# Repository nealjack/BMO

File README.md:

BMO
===

Code, Art and Design files to make BMO from adventure time

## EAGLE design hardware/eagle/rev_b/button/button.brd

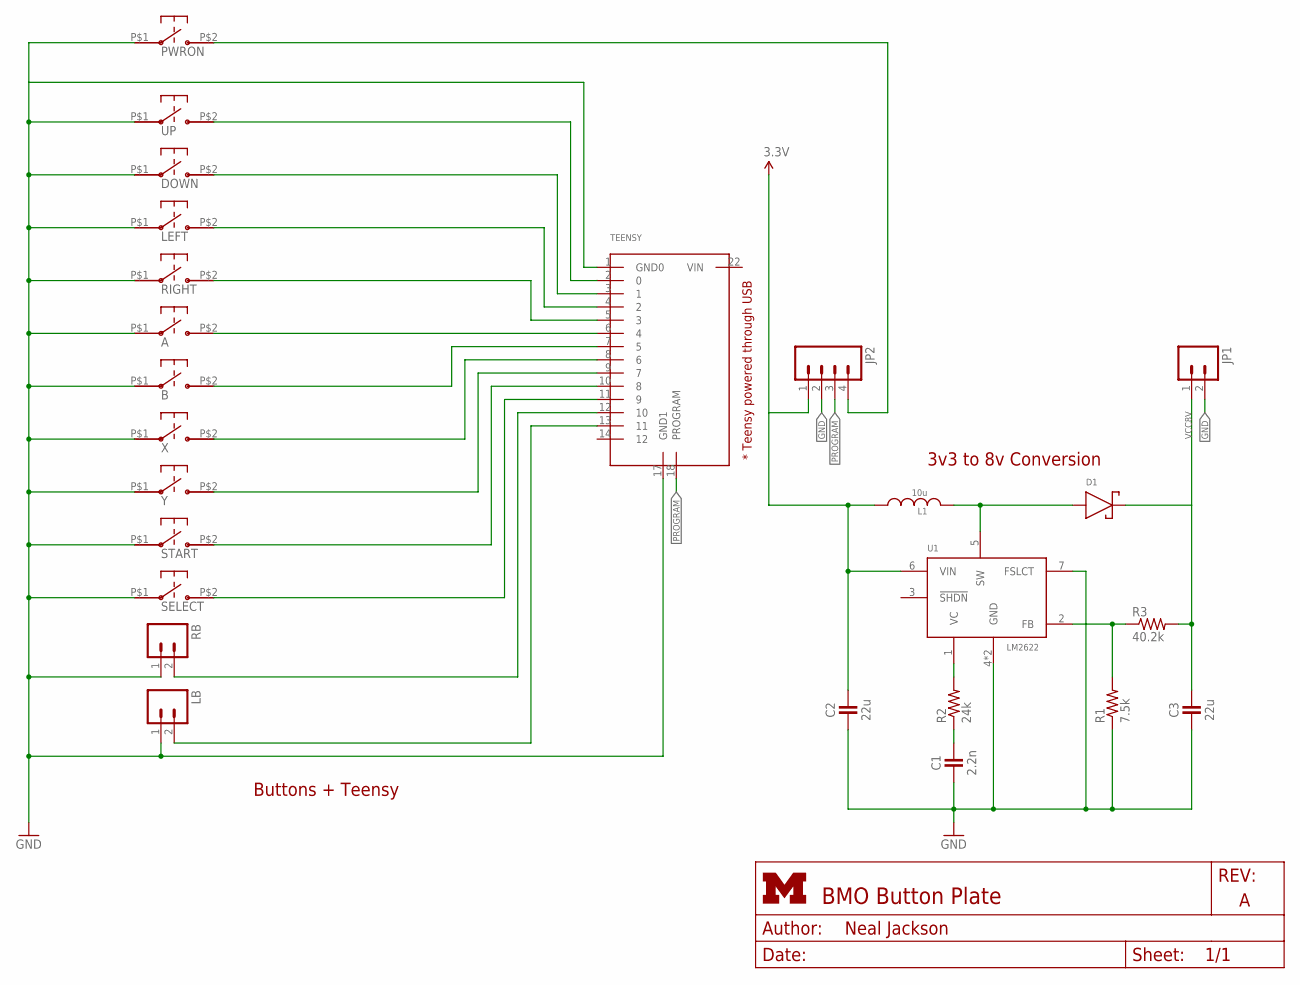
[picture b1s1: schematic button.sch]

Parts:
A: SKPDAMD010
B: SKPDAMD010
C1: 2.2n; 0402_CAP
C2, C3: 22u; 0402_CAP
D1: MBRM140T3G; DO-216AA
DOWN: SKPDAMD010
JP1: M02PTH; 1X02
JP2: M04PTH; 1X04
L1: 10u; 0402_CAP
LB: M02PTH; 1X02
LEFT: SKPDAMD010
PWRON: SKPDAMD010
R1: 7.5k; 0402_RES
R2: 24k; 0402_RES
R3: 40.2k; 0402_RES
RB: M02PTH; 1X02
RIGHT: SKPDAMD010
SELECT: EVQ11D09K
START: EVQ11D09K
TEENSY: TEENSY_LC
U1: LM2622; MSOP8
UP: SKPDAMD010
X: SKPDAMD010
Y: SKPDAMD010

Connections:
3.3V: C2.1, JP2.1, L1.1, U1.6 (VIN)
GND: A.P$1, B.P$1, C1.2, C2.2, C3.2, DOWN.P$1, JP1.2, JP2.2, LB.1, LEFT.P$1, PWRON.P$1, R1.1, RB.1, RIGHT.P$1, SELECT.P$1, START.P$1, TEENSY.1 (GND0), TEENSY.17 (GND1), U1.4 (GND), U1.7 (FSLCT), U1.GND, UP.P$1, X.P$1, Y.P$1
unnamed: A.P$2, TEENSY.6 (4)
unnamed: JP2.4, PWRON.P$2
unnamed: TEENSY.2 (0), UP.P$2
unnamed: DOWN.P$2, TEENSY.3 (1)
unnamed: LEFT.P$2, TEENSY.4 (2)
unnamed: RIGHT.P$2, TEENSY.5 (3)
unnamed: C1.1, R2.1
unnamed: B.P$2, TEENSY.7 (5)
unnamed: TEENSY.8 (6), X.P$2
unnamed: TEENSY.9 (7), Y.P$2
unnamed: START.P$2, TEENSY.10 (8)
unnamed: SELECT.P$2, TEENSY.11 (9)
unnamed: RB.2, TEENSY.12 (10)
unnamed: LB.2, TEENSY.13 (11)
unnamed: R2.2, U1.1 (VC)
unnamed: D1.ANODE, L1.2, U1.5 (SW)
unnamed: R1.2, R3.1, U1.2 (FB)
PROGRAM: JP2.3, TEENSY.18 (PROGRAM)
VCC8V: C3.1, D1.CATHODE, JP1.1, R3.2

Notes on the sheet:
* Teensy powered through USB
Buttons + Teensy
3v3 to 8v Conversion

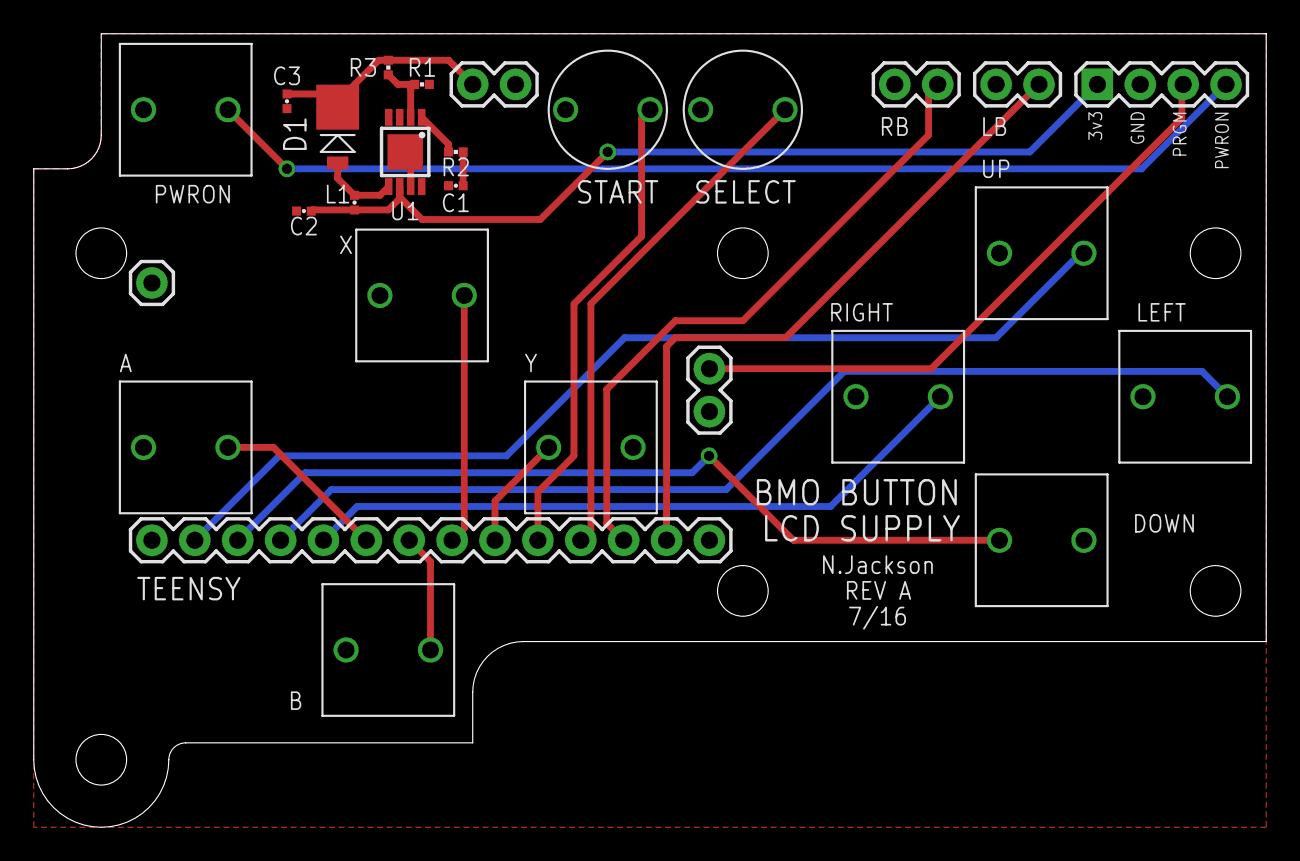
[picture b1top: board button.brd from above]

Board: 2 copper layers, 73.0 x 47.0 mm, 25 parts (0 on the bottom side), 21 nets.

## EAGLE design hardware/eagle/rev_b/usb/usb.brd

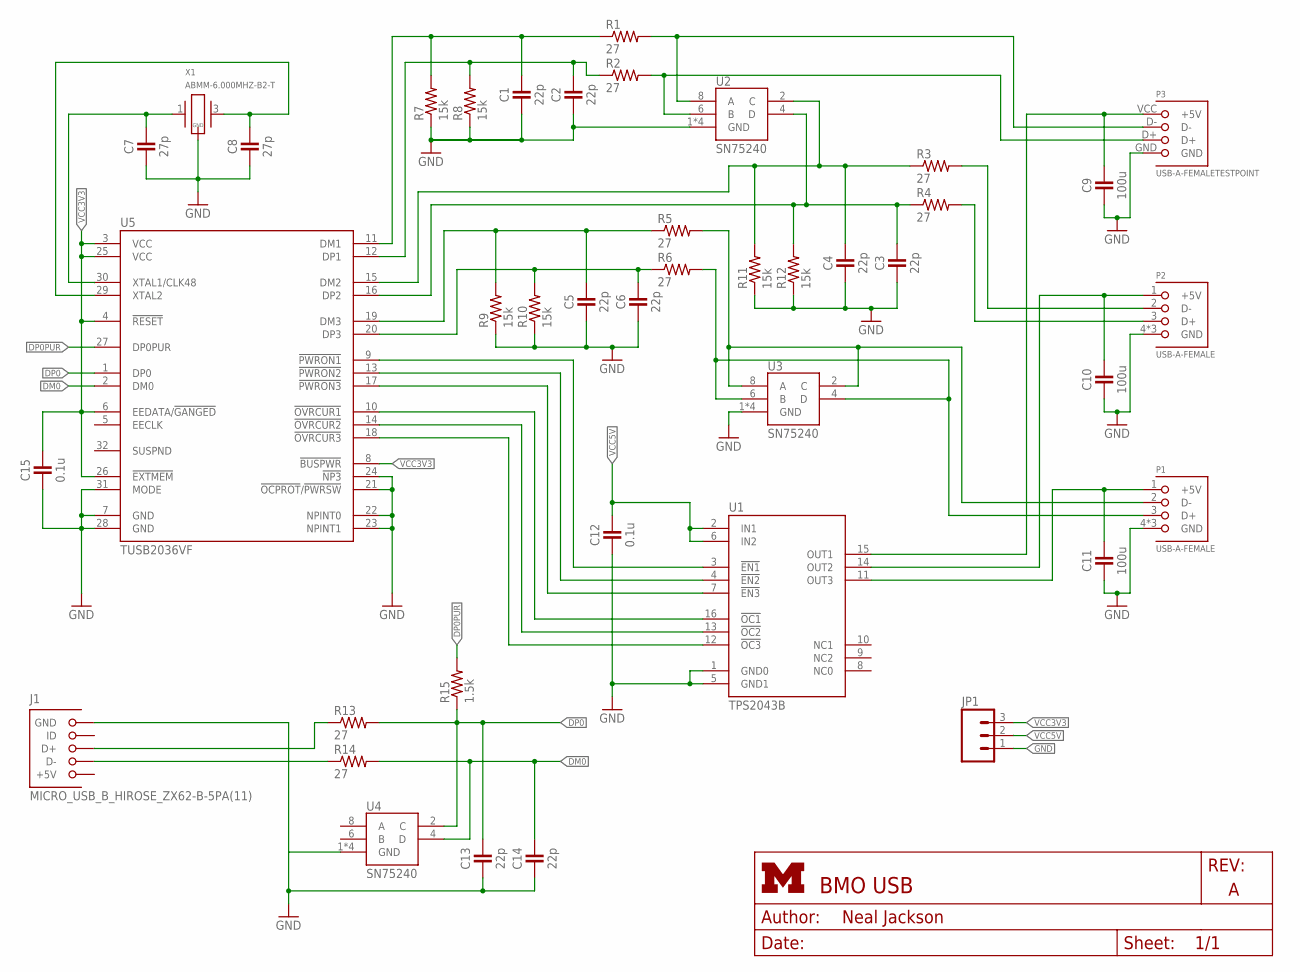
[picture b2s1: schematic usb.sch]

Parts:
C1, C2, C3, C4, C5, C6, C13, C14: 22p; 0402_CAP
C7, C8: 27p; 0402_CAP
C9, C10, C11: 100u; 0402_CAP
C12, C15: 0.1u; 0402_CAP
J1: MICRO_USB_B_HIROSE_ZX62-B-5PA(11); USB_MICRO_B-HIROSE-ZX62-B-5PA(11)
JP1: M03PTH; 1X03
P1, P2: USB-A-FEMALE; 87583-3010RPALF
P3: USB-A-FEMALETESTPOINT; USB-A-TESTPOINT
R1, R2, R3, R4, R5, R6, R13, R14: 27; 0402_RES
R7, R8, R9, R10, R11, R12: 15k; 0402_RES
R15: 1.5k; 0402_RES
U1: TPS2043B; SO16
U2, U3, U4: SN75240; TSSOP8
U5: TUSB2036VF; VF_S-PQFP-G32
X1: ABMM-6.000MHZ-B2-T

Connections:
DM0: C14.1, R14.2, U4.4 (D), U5.2 (DM0)
DP0: C13.1, R13.2, R15.1, U4.2 (C), U5.1 (DP0)
DP0PUR: R15.2, U5.27 (DP0PUR)
GND: C1.2, C2.2, C3.2, C4.2, C5.2, C6.2, C7.2, C8.2, C9.2, C10.2, C11.2, C12.2, C13.2, C14.2, C15.2, J1.5 (GND), JP1.1, P1.4 (GND), P1.P$1 (GND), P1.P$2 (GND), P2.4 (GND), P2.P$1 (GND), P2.P$2 (GND), P3.GND, R7.1, R8.1, R9.1, R10.1, R11.1, R12.1, U1.1 (GND0), U1.5 (GND1), U2.1 (GND), U2.3 (GND), U2.5 (GND), U2.7 (GND), U3.1 (GND), U3.3 (GND), U3.5 (GND), U3.7 (GND), U4.1 (GND), U4.3 (GND), U4.5 (GND), U4.7 (GND), U5.7 (GND), U5.21 (!OCPROT!/!PWRSW!), U5.22 (NPINT0), U5.23 (NPINT1), U5.24 (!NP3), U5.28 (GND), U5.31 (MODE), X1.2 (GND), X1.4 (GND)
unnamed: C7.1, U5.30 (XTAL1/CLK48), X1.1
unnamed: C8.1, U5.29 (XTAL2), X1.3 (2)
unnamed: C11.1, P1.1 (+5V), U1.11 (OUT3)
unnamed: C10.1, P2.1 (+5V), U1.14 (OUT2)
unnamed: C9.1, P3.VCC (+5V), U1.15 (OUT1)
unnamed: P1.2 (D-), R5.2, U3.2 (C), U3.8 (A)
unnamed: P1.3 (D+), R6.2, U3.4 (D), U3.6 (B)
unnamed: P2.3 (D+), R4.2
unnamed: P2.2 (D-), R3.2
unnamed: P3.D+, R2.2, U2.6 (B)
unnamed: P3.D-, R1.2, U2.8 (A)
unnamed: U1.3 (!EN1), U5.9 (!PWRON1)
unnamed: U1.4 (!EN2), U5.13 (!PWRON2)
unnamed: U1.7 (!EN3), U5.17 (!PWRON3)
unnamed: C1.1, R1.1, R7.2, U5.11 (DM1)
unnamed: U1.16 (!OC1), U5.10 (!OVRCUR1)
unnamed: C2.1, R2.1, R8.2, U5.12 (DP1)
unnamed: U1.13 (!OC2), U5.14 (!OVRCUR2)
unnamed: C5.1, R5.1, R9.2, U5.19 (DM3)
unnamed: U1.12 (!OC3), U5.18 (!OVRCUR3)
unnamed: C6.1, R6.1, R10.2, U5.20 (DP3)
unnamed: C4.1, R3.1, R11.2, U2.2 (C), U5.15 (DM2)
unnamed: C3.1, R4.1, R12.2, U2.4 (D), U5.16 (DP2)
unnamed: J1.2 (D-), R14.1
unnamed: J1.3 (D+), R13.1
VCC3V3: C15.1, JP1.3, U5.3 (VCC), U5.4 (!RESET), U5.6 (EEDATA/!GANGED), U5.8 (!BUSPWR), U5.25 (VCC), U5.26 (!EXTMEM)
VCC5V: C12.1, JP1.2, U1.2 (IN1), U1.6 (IN2)

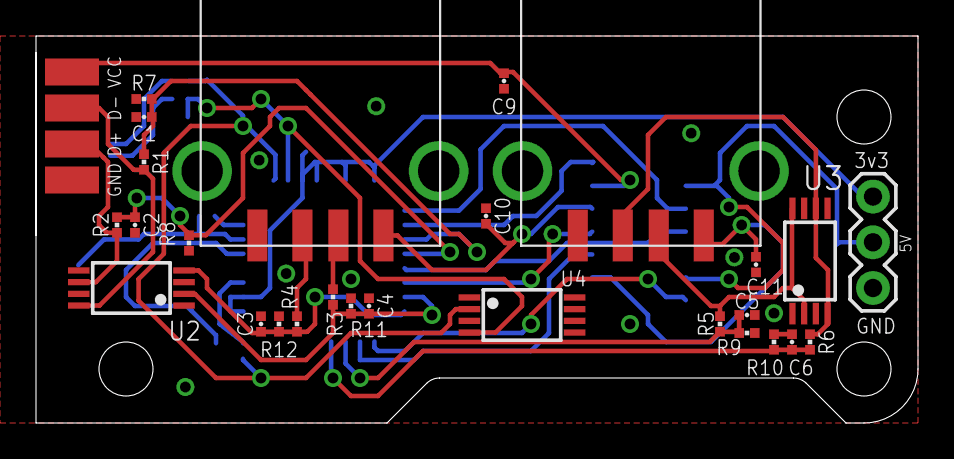
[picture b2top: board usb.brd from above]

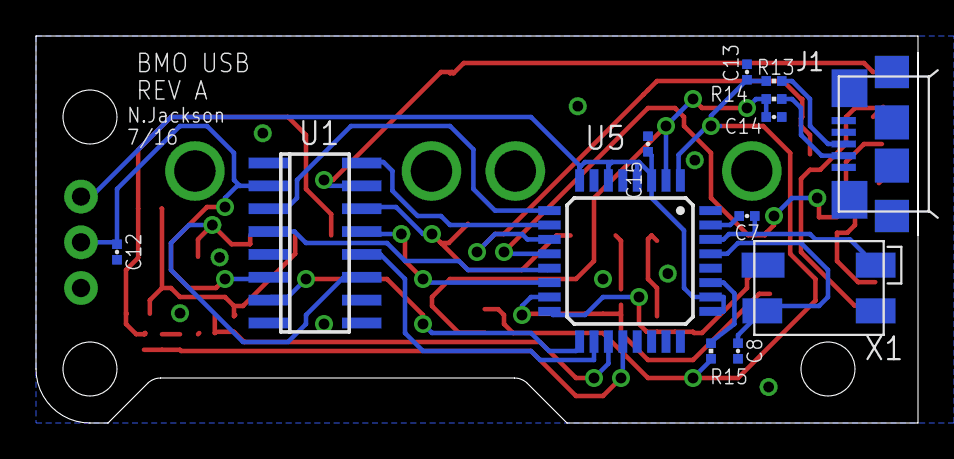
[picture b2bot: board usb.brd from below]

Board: 2 copper layers, 49.0 x 21.5 mm, 41 parts (13 on the bottom side), 31 nets.

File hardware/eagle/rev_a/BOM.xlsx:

Qty | Value | Device | Package | Parts | Description | MOUSER | DIGIKEY
1 | 10u | INDUCTOR0402 | 0402_CAP | L1 |  |  | 445-3608-1-ND
1 | 2.2n | CAPACITOR | 0402_CAP | C1 | 0402 Capacitor |  | 490-6359-1-ND
2 | 22u | CAPACITOR | 0402_CAP | C2, C3 | 0402 Capacitor |  | 490-10476-1-ND
1 | 24k | RESISTOR0402_RES | 0402_RES | R2 | Resistor |  | P24.0KLCT-ND
1 | 40.2k | RESISTOR0402_RES | 0402_RES | R3 | Resistor |  | P40.2KLCT-ND
1 | 7.5k | RESISTOR0402_RES | 0402_RES | R1 | Resistor |  | RHM7.5KCDCT-ND
2 | EVQ11D09K | EVQ11D09K | EVQ11D09K | SELECT, START |  |  | P15933SCT-ND
1 | LM2622 | LM2622 | MSOP8 | U1 |  |  | 296-35404-1-ND
1 | MBRM140T3G | MBRM140T3G | DO-216AA | D1 |  |  | MBRM140T3GOSCT-ND
11 | SKPDAMD010 | SKPDAMD010 | SKPDAMD010 | A, B, DOWN, LEFT, PWRON, RIGHT, UP, X, Y, RB, LB |  | 688-SKPDAM
1 | TEENSY_LC | TEENSY_LC | TEENSY_LC | TEENSY |  | 485-2419
2 | MICRO_USB_B_HIROSE_ZX62-B-5PA(33) | MICRO_USB_B_HIROSE_ZX62-B-5PA(33) | USB_MICRO_B-HIROSE-ZX62-B-5PA(33) | J1 | Connector Receptacle USB - micro B 2.0 5 Position Surface Mount, Right Angle, H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 |  | H125270CT-ND
For the USB Board:
Qty | Value | Device | Package | Parts | Description | MOUSER | DIGIKEY
2 | 0.1u | CAPACITOR | 0402_CAP | C12, C15 | 0402 Capacitor |  | 490-6328-1-ND
1 | 1.5k | RESISTOR0402_RES | 0402_RES | R15 | Resistor |  | P1.50KLCT-ND
3 | 100u | CAPACITOR | 0402_CAP | C9, C10, C11 | 0402 Capacitor |  | 490-13244-1-ND
6 | 15k | RESISTOR0402_RES | 0402_RES | R7, R8, R9, R10, R11, R12 | Resistor |  | P15.0KLCT-ND
8 | 22p | CAPACITOR | 0402_CAP | C1, C2, C3, C4, C5, C6, C13, C14 | 0402 Capacitor |  | 490-11382-1-ND
8 | 27 | RESISTOR0402_RES | 0402_RES | R1, R2, R3, R4, R5, R6, R13, R14 | Resistor |  | P27.0LCT-ND
2 | 27p | CAPACITOR | 0402_CAP | C7, C8 | 0402 Capacitor |  | 490-6224-1-ND
1 | ABMM-6.000MHZ-B2-T | ABMM-6.000MHZ-B2-T | ABMM-6.000MHZ-B2-T | X1 |  |  | 535-10156-1-ND
3 | SN75240 | SN75240 | TSSOP8 | U2, U3, U4 |  |  | 296-6596-1-ND
1 | TPS2043B | TPS2043B | SO16 | U1 |  |  | 296-17211-5-ND
1 | TUSB2036VF | TUSB2036VF | VF_S-PQFP-G32 | U5 | 2/3 port Hub for the Universal serial bus with optional serial EEPROM Interface |  | 296-27129-1-ND
2 | USB-A-FEMALE | USB-A-FEMALE | 87583-3010RPALF | P1, P2 |  |  | 609-4946-1-ND

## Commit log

2014-07-27 initial push
2014-07-27 cleaned up body dir
2016-04-28 reorganization
2016-04-28 schematic for button pcb
2016-06-26 Start of button PCB Need to fit teensy on same board, reduce the amount of mapped out pins
2016-07-01 First stab at button board Fits current body model, faceplate needs spacing of start/select
2016-07-01 Designs largely finished for body and front
2016-07-01 Back and panel not quite done or tested, but should fit
2016-07-02 Start USB board, add some usb hub parts to lbr
2016-07-02 Tweak back panel; add other unfinished designs
2016-07-03 finished usb schematic
2016-07-04 start of board, might need to restart
2016-07-04 usb board done
2016-07-04 tweaking size, added power header
2016-07-05 cleanup
2016-07-05 Fitted board to case, added silkscreen
2016-07-05 fix one last cap
2016-07-06 Tweaks to body and integration of chip holder
2016-07-07 Added boards for back buttons and charging/serial port Tweaks and redesigns for button/usb boards to fit in case better
2016-07-07 Shipped to OSHPark added merge.cfg for use with gerbmerge
2016-07-08 added bom, need to combine
2016-07-08 Added BOM Next rev needs to change pad sizes for 0603 and larger parts I forgot to take into account the sizing of inductors and caps with larger values. C9,C10,C11 are set to 47uF for this rev, shou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
2017-05-11 random changes not committed from this summer
2017-05-27 add full teensy layout
2017-05-27 start revb
2026-05-03 Add wip power board
2026-05-03 wip start ltc4412 addition
2026-06-13 Placed and routed everything. DRC is clean.
2026-06-13 rename to bmo_power for power board
2026-06-14 embed 3d models
2026-06-14 first try adding kibot
2026-06-14 add workflow dispatch option
2026-06-14 fix paths

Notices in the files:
parts and their libraries:
SparkFun-Connectors: Licensing: CC v3.0 Share-Alike You are welcome to use this library for commercial purposes.
